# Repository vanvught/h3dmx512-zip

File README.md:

<br>[PayPal.Me Donate](https://paypal.me/AvanVught?locale.x=nl_NL)

# Orange Pi Zero / Orange Pi One
Open Source and Open Source Hardware.
<br>
## SDCard

**First time setup**: Select the uboot-*.zip for your board. Unzip the file and use an img writer; for example [Etcher](https://etcher.io).

U-Boot Orange Pi Zero: [uboot-orangpi_zero.zip](https://github.com/vanvught/h3dmx512-zip/blob/master/uboot-orangpi_zero.zip?raw=true)

U-Boot Orange Pi One: [uboot-orangpi_one.zip](https://github.com/vanvught/h3dmx512-zip/blob/master/uboot-orangpi_one.zip?raw=true)

**Firmware uImage**

Orange Pi Zero: From the zip file, copy file `orangepi_zero.uImage.gz`to the SDCard and rename to `uImage`

Orange Pi One: From the zip file, copy file `orangepi_one.uImage.gz`to the SDCard and rename to `uImage`

## Firmware uImage

* **Ethernet**
  * **Art-Net 4**
      * Pixel controller **WS28xx/SK6812/APA102/UCSx903/P9813** with DMX [Orange Pi Zero]
         * 1x 4 Universes [1x DMX] {[zip](https://github.com/vanvught/h3dmx512-zip/blob/master/opi_emac_artnet_pixel_dmx.zip?raw=true)}
         * 8x 4 Universes [2x DMX] {[zip](https://github.com/vanvught/h3dmx512-zip/blob/master/opi_emac_artnet_pixel_dmx_multi.zip?raw=true)}
      * DMX Input/Output Node / **RDM** Controller
         *  1 Port {[zip](https://github.com/vanvught/h3dmx512-zip/blob/master/opi_emac_artnet_dmx.zip?raw=true)} {*Orange Pi Zero*}
         *  2 Ports {[zip](https://github.com/vanvught/h3dmx512-zip/blob/master/opi_emac_artnet_dmx_multi.zip?raw=true)} {*Orange Pi Zero*}
         *  4 Ports {[zip](https://github.com/vanvught/h3dmx512-zip/blob/master/opi_emac_artnet_dmx_multi.zip?raw=true)} {*Orange Pi One*}
      * **Real-time Monitor** 1 Universe {[zip](https://github.com/vanvught/h3dmx512-zip/blob/master/opi_emac_artnet_monitor.zip?raw=true)} {*Orange Pi One - HDMI output*}
     * Stepper controller **L6470 RDM**
         * Sparkfun AutoDriver chaining {[zip](https://github.com/vanvught/h3dmx512-zip/blob/master/opi_emac_artnet_rdm_l6470.zip?raw=true)} {*Orange Pi Zero*}
  * **sACN E1.31** 
      * Pixel Controller **WS28xx/SK6812/APA102/UCSx903/P9813** with DMX [Orange Pi Zero]
         *  1x 4 Universes [1x DMX] {[zip](https://github.com/vanvught/h3dmx512-zip/blob/master/opi_emac_e131_pixel_dmx.zip?raw=true)}
         *  8x 4 Universes [2x DMX] {[zip](https://github.com/vanvught/h3dmx512-zip/blob/master/opi_emac_e131_pixel_dmx_multi.zip?raw=true)}
      * DMX Input / Output Bridge
         *  2 Ports {[zip](https://github.com/vanvught/h3dmx512-zip/blob/master/opi_emac_e131_dmx_multi.zip?raw=true)} {*Orange Pi Zero*}
         *  4 Ports {[zip](https://github.com/vanvught/h3dmx512-zip/blob/master/opi_emac_e131_dmx_multi.zip?raw=true)} {*Orange Pi One*}
      * **Real-time Monitor** 1 Universe {[zip](https://github.com/vanvught/h3dmx512-zip/blob/master/opi_emac_e131_monitor.zip?raw=true)} {*Orange Pi One - HDMI output*}
      * **Art-Net** converter 4/32 Universes {[zip](https://github.com/vanvught/h3dmx512-zip/blob/master/opi_emac_e131_artnet.zip?raw=true)} {*Orange Pi Zero*}
  * **Distributed Display Protocol (DDP)**
      *  Pixel Controller **WS28xx/SK6812/APA102/UCSx903/P9813** with DMX [Orange Pi Zero]
         * 8x 680 RGB or 8x 512 RGBW [2x DMX Out] {[zip](https://github.com/vanvught/h3dmx512-zip/blob/master/opi_emac_ddp_pixel_dmx_multi.zip?raw=true)}
  * **OSC** 
      * DMX Bridge {[zip](https://github.com/vanvught/h3dmx512-zip/blob/master/opi_emac_osc_dmx.zip?raw=true)}
      * Pixel Controller (WS28xx/SK6812/APA102/UCSx903/P9813) {[zip](https://github.com/vanvught/h3dmx512-zip/blob/master/opi_emac_osc_pixel.zip?raw=true)}
      * Client with support for buttons {[zip](https://github.com/vanvught/h3dmx512-zip/blob/master/opi_emac_osc_client.zip?raw=true)}
      * **Real-time Monitor** 1 Universe {[zip](https://github.com/vanvught/h3dmx512-zip/blob/master/opi_emac_osc_monitor.zip?raw=true)} {*Orange Pi One - HDMI output*}
  * **Showfile**
      *  **Player** {[zip](https://github.com/vanvught/h3dmx512-zip/blob/master/opi_emac_showfile.zip?raw=true)}
* **RDM** 
  * Controller with USB [Compatible with **Enttec USB Pro protocol**] {[zip](https://github.com/vanvught/h3dmx512-zip/blob/master/opi_dmx_usb_pro.zip?raw=true)} {*Orange Pi Zero*}
  * Responder / **DMX Pixel Controller (WS28xx/SK6812/APA102/UCSx903/P9813)** {[zip](https://github.com/vanvught/h3dmx512-zip/blob/master/opi_rdm_responder.zip?raw=true)} {*Orange Pi Zero*}
  * Stepper controller L6470
     * Sparkfun AutoDriver chaining {[zip](https://github.com/vanvught/h3dmx512-zip/blob/master/opi_rdm_responder_l6470.zip?raw=true)} {*Orange Pi Zero*}
     * Roboteurs SlushEngine Model X LT {[zip](https://github.com/vanvught/h3dmx512-zip/blob/master/opi_rdm_responder_l6470.zip?raw=true)} {*Orange Pi One*}
* **DMX**
  * **Real-time Monitor** {[zip](https://github.com/vanvught/h3dmx512-zip/blob/master/opi_dmx_monitor.zip?raw=true)} {*Orange Pi One - HDMI output*}
* **SMPTE LTC**
  * **LTC SMPTE Timecode** Reader / Writer / Generator {[zip](https://github.com/vanvught/h3dmx512-zip/blob/master/opi_emac_ltc_smpte.zip?raw=true)}  {*Orange Pi Zero*}
* **MIDI**
  *  **Real-time Monitor** {[zip](https://github.com/vanvught/h3dmx512-zip/blob/master/opi_midi_monitor.zip?raw=true)}  {*Orange Pi One - HDMI output*}

All implementations are fully according to the standards.
<br>

Detailed information can be found here : [http://www.orangepi-dmx.org](http://www.orangepi-dmx.org)

## Orange Pi Firmware Update UI
[https://github.com/vanvught/h3dmx512-Firmware-Update-UI/releases](https://github.com/vanvught/h3dmx512-Firmware-Update-UI/releases)<br>

<br>

## Remote Configuration Manager [Legacy]
[https://github.com/vanvught/Remote-Config-UI/releases](https://github.com/vanvught/Remote-Config-UI/releases)<br>

<br>

## Wireshark LUA plugin's
[https://github.com/vanvught/wireshark](https://github.com/vanvught/wireshark)

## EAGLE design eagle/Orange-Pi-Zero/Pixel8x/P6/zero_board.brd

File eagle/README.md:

# EAGLE 6.4.0 or higher
## Orange Pi Zero - prototype boards

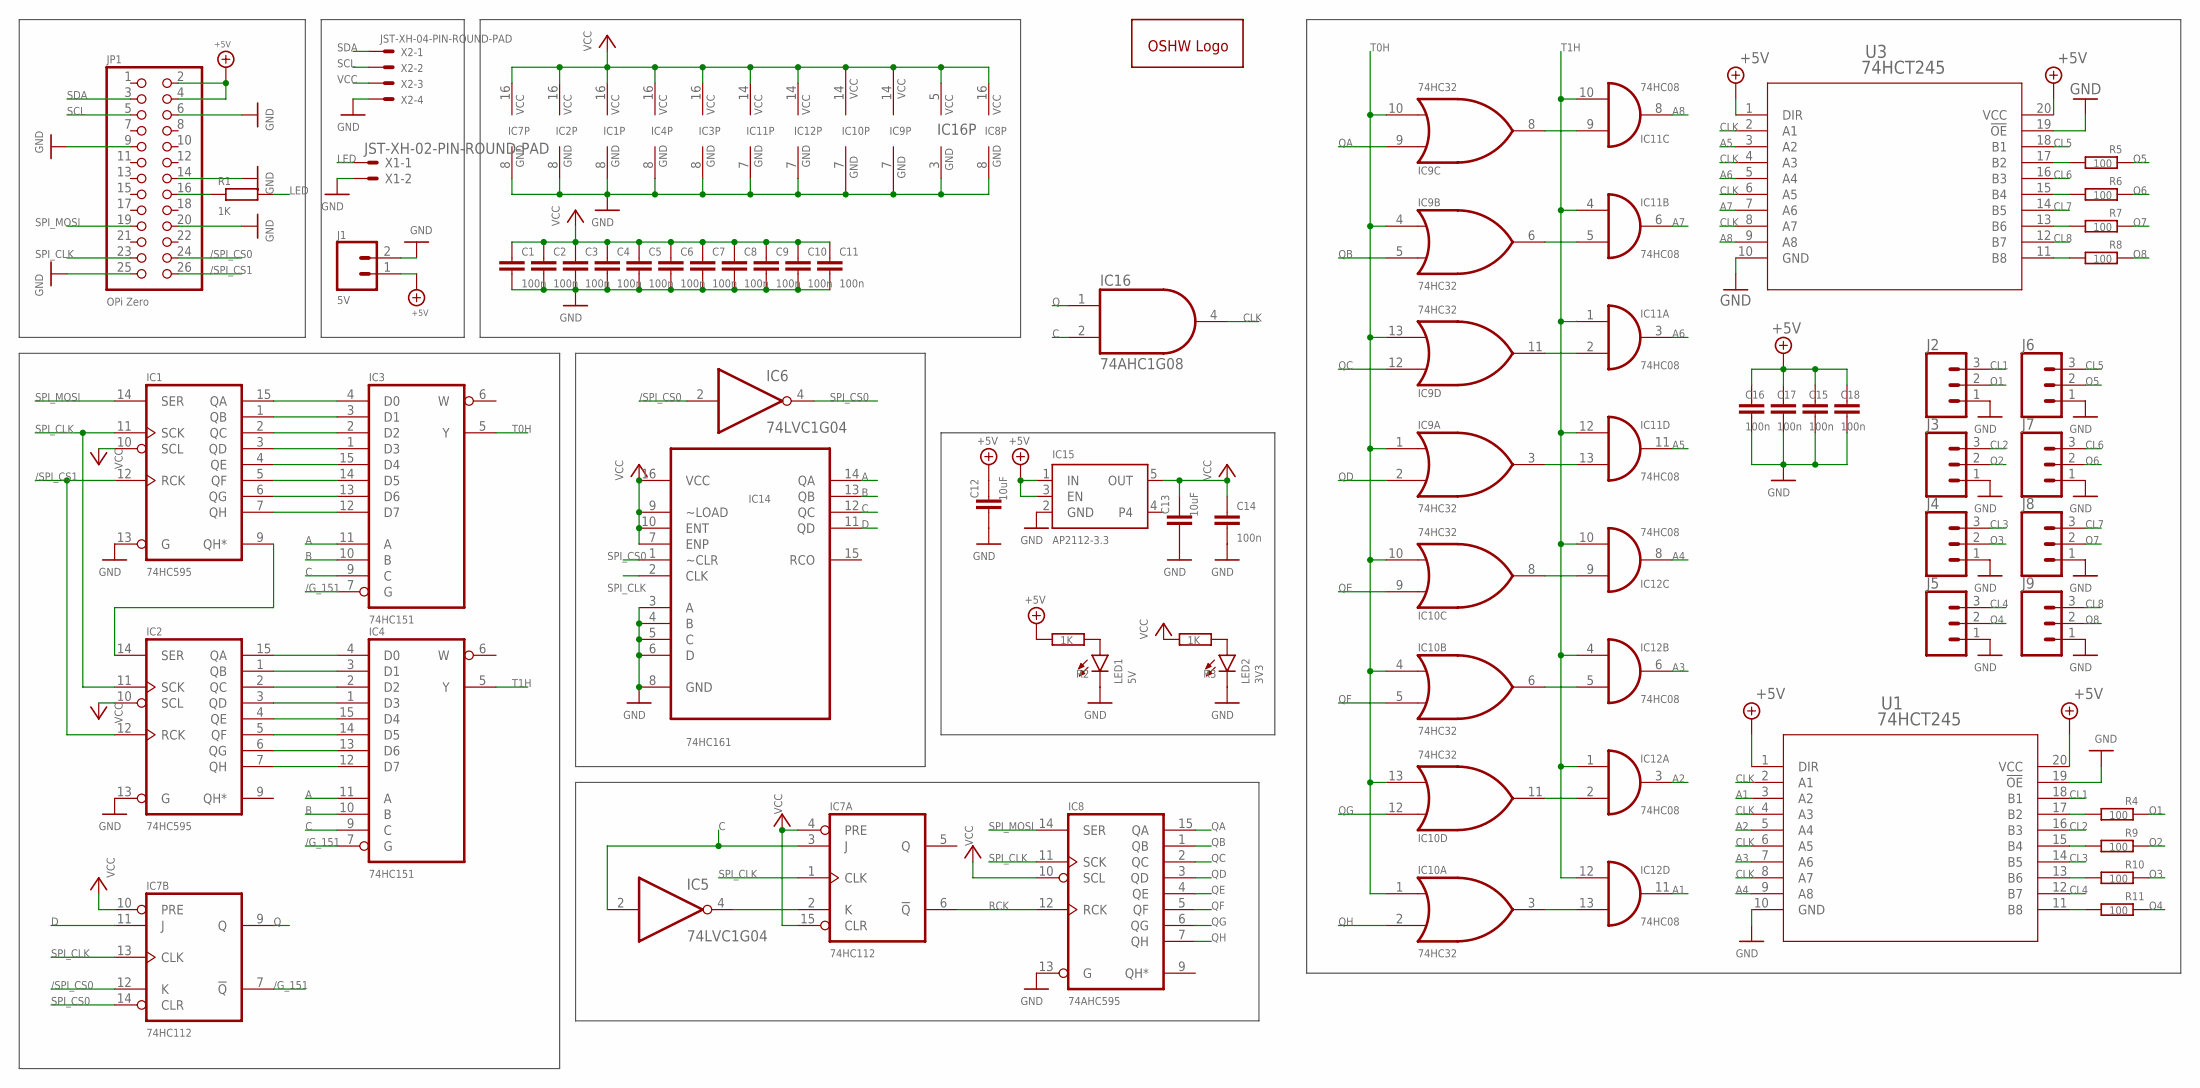
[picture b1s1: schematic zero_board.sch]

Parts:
C1, C2, C3, C4, C5, C6, C7, C8, C9, C10, C11, C14, C15, C16, C17, C18: 100n; C0603
C12, C13: 10uF; C0805
GOLD_ORB_SM1: OSHWLOGOLOGO5MM; OSHW_5MM
IC1, IC2: 74HC595; SO16
IC3, IC4: 74HC151; SO16
IC5, IC6: 74LVC1G04; SC70-5
IC7: 74HC112; SO16
IC8: 74AHC595; SO16
IC9, IC10: 74HC32; SO14
IC11, IC12: 74HC08; SO14
IC14: 74HC161; SOIC127P600X175-16N
IC15: AP2112-3.3; SOT23-5
IC16: 74AHC1G08; SC70-5
J1: 5V; SCREWTERMINAL-3.5MM-2
J2, J3, J4, J5, J6, J7, J8, J9: CONN_03SCREW-NS; SCREWTERMINAL-3.5MM-3-NS
JP1: OPi Zero; 2X13
LED1: 5V; CHIP-LED0603
LED2: 3V3; CHIP-LED0603
R1, R2, R3: 1K; R0603
R4, R5, R6, R7, R8, R9, R10, R11: 100; R0603
U1, U3: 74HCT245; PW20
X1: JST-XH-02-PIN-ROUND-PAD; JST-XH-02-PACKAGE-ROUND-PAD
X2: JST-XH-04-PIN-ROUND-PAD; JST-XH-04-PACKAGE-ROUND-PAD

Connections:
+5V: C12.1, C15.1, C16.1, C17.1, C18.1, IC15.1 (IN), IC15.3 (EN), J1.1, JP1.2, JP1.4, R2.1, U1.1 (DIR), U1.20 (VCC), U3.1 (DIR), U3.20 (VCC)
/G_151: IC3.7 (G), IC4.7 (G), IC7.7 (!Q)
/SPI_CS0: IC6.2 (I), IC7.12 (K), JP1.24
/SPI_CS1: IC1.12 (RCK), IC2.12 (RCK), JP1.26
A: IC3.11 (A), IC4.11 (A), IC14.14 (QA)
A1: IC12.11 (O), U1.3 (A2)
A2: IC12.3 (O), U1.5 (A4)
A3: IC12.6 (O), U1.7 (A6)
A4: IC12.8 (O), U1.9 (A8)
A5: IC11.11 (O), U3.3 (A2)
A6: IC11.3 (O), U3.5 (A4)
A7: IC11.6 (O), U3.7 (A6)
A8: IC11.8 (O), U3.9 (A8)
B: IC3.10 (B), IC4.10 (B), IC14.13 (QB)
C: IC3.9 (C), IC4.9 (C), IC5.2 (I), IC7.3 (J), IC14.12 (QC), IC16.2 (I1)
CL1: J2.3, U1.18 (B1)
CL2: J3.3, U1.16 (B3)
CL3: J4.3, U1.14 (B5)
CL4: J5.3, U1.12 (B7)
CL5: J6.3, U3.18 (B1)
CL6: J7.3, U3.16 (B3)
CL7: J8.3, U3.14 (B5)
CL8: J9.3, U3.12 (B7)
CLK: IC16.4 (O), U1.2 (A1), U1.4 (A3), U1.6 (A5), U1.8 (A7), U3.2 (A1), U3.4 (A3), U3.6 (A5), U3.8 (A7)
D: IC7.11 (J), IC14.11 (QD)
GND: C1.2, C2.2, C3.2, C4.2, C5.2, C6.2, C7.2, C8.2, C9.2, C10.2, C11.2, C12.2, C13.2, C14.2, C15.2, C16.2, C17.2, C18.2, IC1.8 (GND), IC1.13 (G), IC2.8 (GND), IC2.13 (G), IC3.8 (GND), IC4.8 (GND), IC5.3 (GND), IC6.3 (GND), IC7.8 (GND), IC8.8 (GND), IC8.13 (G), IC9.7 (GND), IC10.7 (GND), IC11.7 (GND), IC12.7 (GND), IC14.3 (A), IC14.4 (B), IC14.5 (C), IC14.6 (D), IC14.8 (GND), IC15.2 (GND), IC16.3 (GND), J1.2, J2.1, J3.1, J4.1, J5.1, J6.1, J7.1, J8.1, J9.1, JP1.6, JP1.9, JP1.14, JP1.20, JP1.25, LED1.C, LED2.C, U1.10 (GND), U1.19 (!OE), U3.10 (GND), U3.19 (!OE), X1.2, X2.4
LED: R1.2, X1.1
unnamed: IC10.11 (O), IC12.2 (I1)
unnamed: IC10.6 (O), IC12.5 (I1)
unnamed: IC10.8 (O), IC12.9 (I0)
unnamed: IC10.3 (O), IC12.13 (I1)
unnamed: IC9.8 (O), IC11.9 (I0)
unnamed: IC9.6 (O), IC11.5 (I1)
unnamed: IC9.11 (O), IC11.2 (I1)
unnamed: JP1.16, R1.1
unnamed: R11.1, U1.11 (B8)
unnamed: R8.1, U3.11 (B8)
unnamed: IC1.15 (QA), IC3.4 (D0)
unnamed: IC1.1 (QB), IC3.3 (D1)
unnamed: IC1.2 (QC), IC3.2 (D2)
unnamed: IC1.3 (QD), IC3.1 (D3)
unnamed: IC5.4 (O), IC7.2 (K)
unnamed: IC9.3 (O), IC11.13 (I1)
unnamed: R7.1, U3.13 (B6)
unnamed: IC2.15 (QA), IC4.4 (D0)
unnamed: R10.1, U1.13 (B6)
unnamed: IC1.4 (QE), IC3.15 (D4)
unnamed: IC1.5 (QF), IC3.14 (D5)
unnamed: IC1.6 (QG), IC3.13 (D6)
unnamed: IC1.7 (QH), IC3.12 (D7)
unnamed: IC2.1 (QB), IC4.3 (D1)
unnamed: R6.1, U3.15 (B4)
unnamed: IC2.2 (QC), IC4.2 (D2)
unnamed: IC2.3 (QD), IC4.1 (D3)
unnamed: IC2.4 (QE), IC4.15 (D4)
unnamed: IC2.5 (QF), IC4.14 (D5)
unnamed: IC2.6 (QG), IC4.13 (D6)
unnamed: IC2.7 (QH), IC4.12 (D7)
unnamed: R5.1, U3.17 (B2)
unnamed: LED1.A, R2.2
unnamed: LED2.A, R3.2
unnamed: R9.1, U1.15 (B4)
unnamed: R4.1, U1.17 (B2)
unnamed: IC1.9 (QH*), IC2.14 (SER)
O1: J2.2, R4.2
O2: J3.2, R9.2
O3: J4.2, R10.2
O4: J5.2, R11.2
O5: J6.2, R5.2
O6: J7.2, R6.2
O7: J8.2, R7.2
O8: J9.2, R8.2
Q: IC7.9 (Q), IC16.1 (I0)
QA: IC8.15 (QA), IC9.9 (I0)
QB: IC8.1 (QB), IC9.5 (I1)
QC: IC8.2 (QC), IC9.12 (I0)
QD: IC8.3 (QD), IC9.2 (I1)
QE: IC8.4 (QE), IC10.9 (I0)
QF: IC8.5 (QF), IC10.5 (I1)
QG: IC8.6 (QG), IC10.12 (I0)
QH: IC8.7 (QH), IC10.2 (I1)
RCK: IC7.6 (!Q), IC8.12 (RCK)
SCL: JP1.5, X2.2
SDA: JP1.3, X2.1
SPI_CLK: IC1.11 (SCK), IC2.11 (SCK), IC7.1 (CLK), IC7.13 (CLK), IC8.11 (SCK), IC14.2 (CLK), JP1.23
SPI_CS0: IC6.4 (O), IC7.14 (CLR), IC14.1 (~CLR)
SPI_MOSI: IC1.14 (SER), IC8.14 (SER), JP1.19
T0H: IC3.5 (Y), IC9.1 (I0), IC9.4 (I0), IC9.10 (I1), IC9.13 (I1), IC10.1 (I0), IC10.4 (I0), IC10.10 (I1), IC10.13 (I1)
T1H: IC4.5 (Y), IC11.1 (I0), IC11.4 (I0), IC11.10 (I1), IC11.12 (I0), IC12.1 (I0), IC12.4 (I0), IC12.10 (I1), IC12.12 (I0)
VCC: C1.1, C2.1, C3.1, C4.1, C5.1, C6.1, C7.1, C8.1, C9.1, C10.1, C11.1, C13.1, C14.1, IC1.10 (SCL), IC1.16 (VCC), IC2.10 (SCL), IC2.16 (VCC), IC3.16 (VCC), IC4.16 (VCC), IC5.5 (VCC), IC6.5 (VCC), IC7.4 (PRE), IC7.10 (PRE), IC7.15 (CLR), IC7.16 (VCC), IC8.10 (SCL), IC8.16 (VCC), IC9.14 (VCC), IC10.14 (VCC), IC11.14 (VCC), IC12.14 (VCC), IC14.7 (ENP), IC14.9 (~LOAD), IC14.10 (ENT), IC14.16 (VCC), IC15.5 (OUT), IC16.5 (VCC), R3.1, X2.3

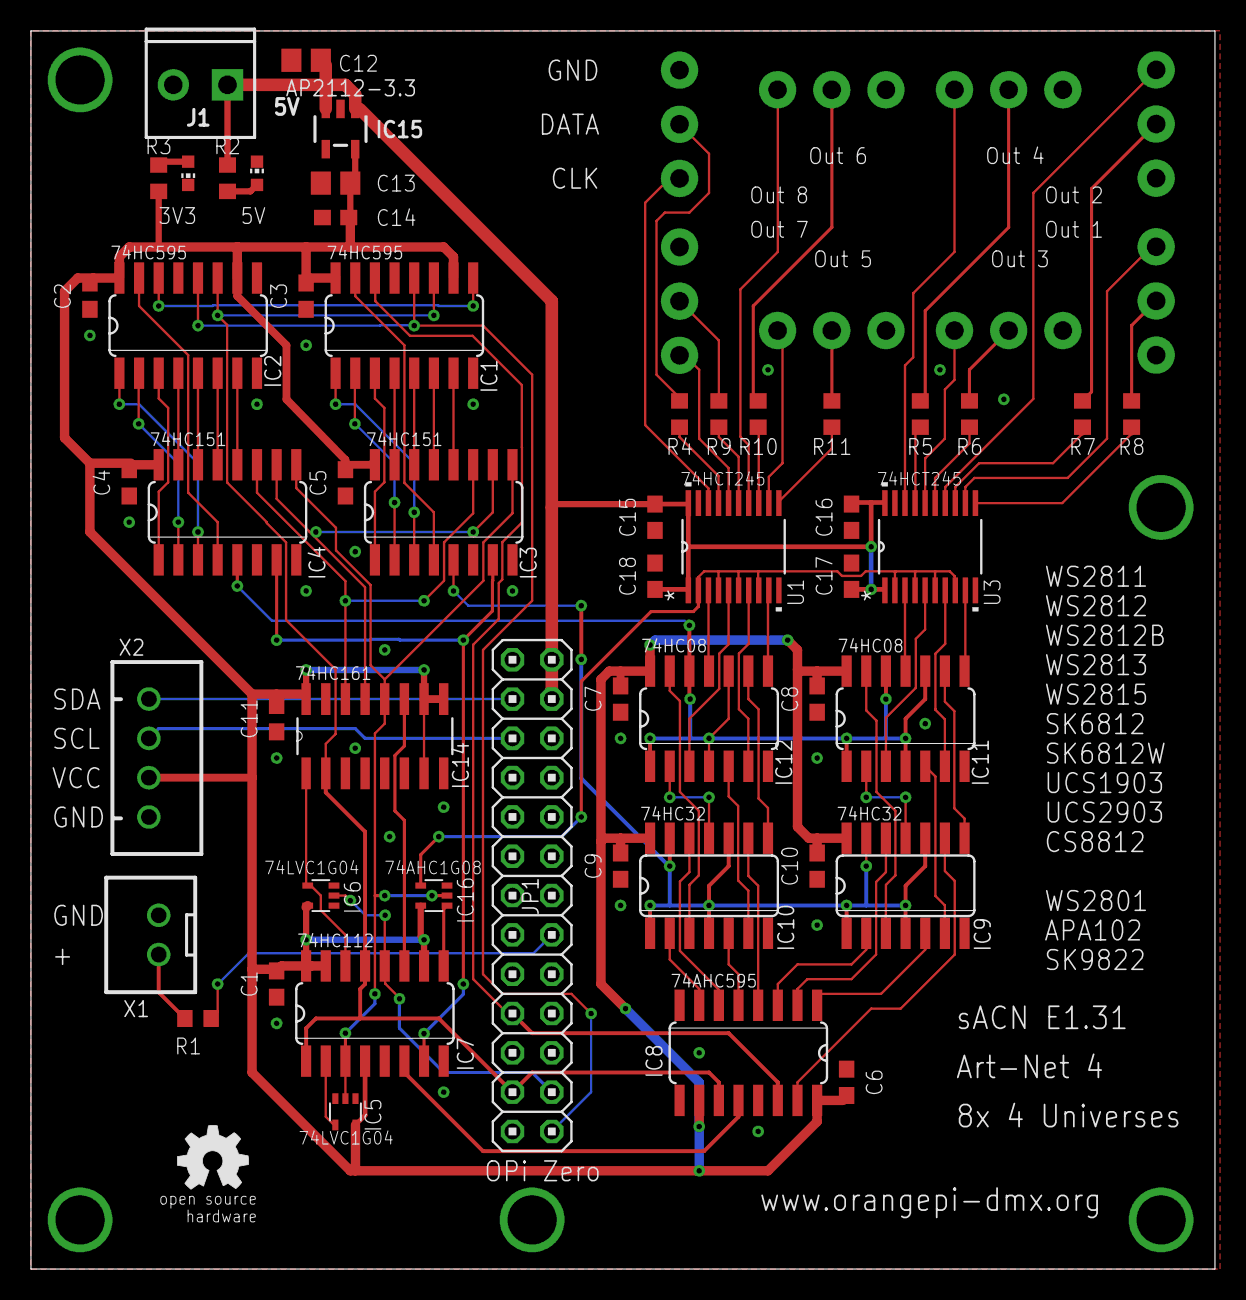
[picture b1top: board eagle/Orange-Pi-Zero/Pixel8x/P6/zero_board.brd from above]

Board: 2 copper layers, 76.5 x 80.0 mm, 61 parts (0 on the bottom side), 90 nets.

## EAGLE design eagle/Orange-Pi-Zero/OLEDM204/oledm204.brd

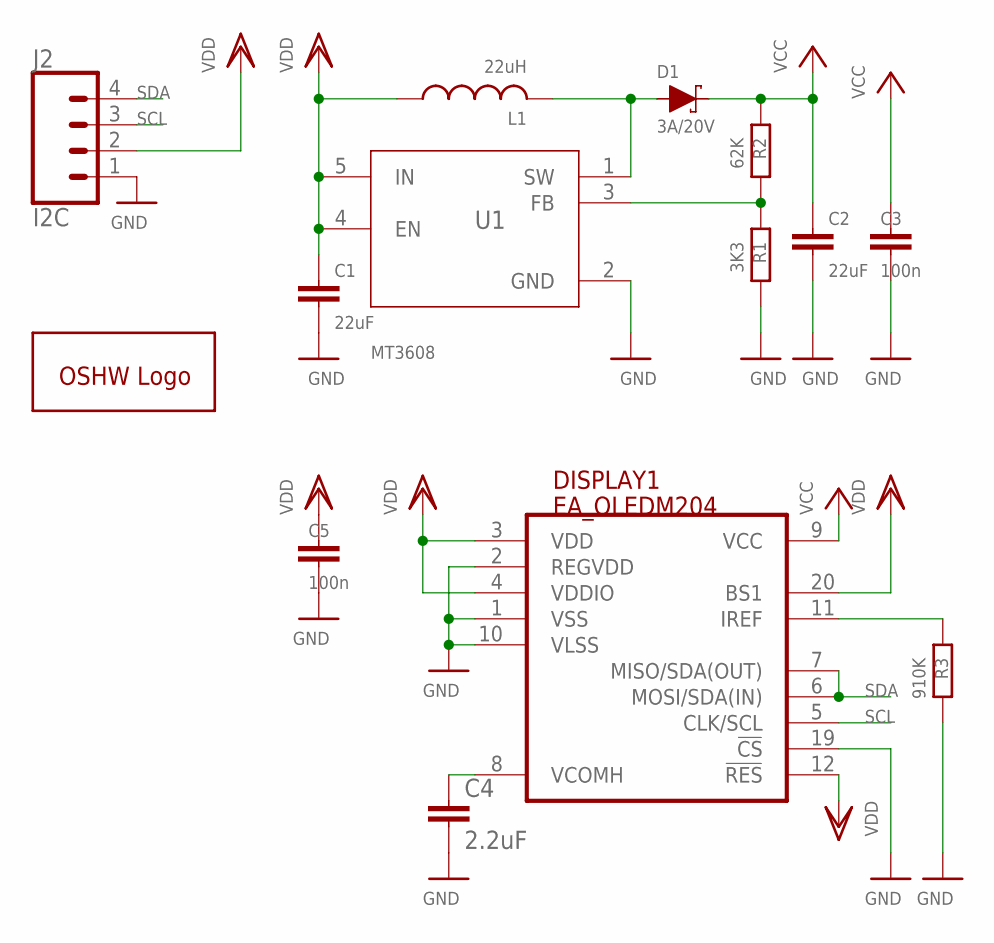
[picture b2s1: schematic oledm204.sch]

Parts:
C1, C2: 22uF; C0603
C3, C5: 100n; C0603
C4: 2.2uF; C0603
D1: 3A/20V; SMA-DIODE
DISPLAY1: EA_OLEDM204
GOLD_ORB_SM1: OSHWLOGOLOGO5MM; OSHW_5MM
J2: I2C; 1X04
L1: 22uH; PIS2816
R1: 3K3; R0402
R2: 62K; R0402
R3: 910K; R0402
U1: MT3608; SOT95P280X145-6N

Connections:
GND: C1.2, C2.2, C3.2, C4.2, C5.2, DISPLAY1.1 (VSS), DISPLAY1.2 (REGVDD), DISPLAY1.10 (VLSS), DISPLAY1.19 (!CS!), J2.1, R1.2, R3.2, U1.2 (GND)
unnamed: DISPLAY1.11 (IREF), R3.1
unnamed: R1.1, R2.2, U1.3 (FB)
unnamed: D1.A, L1.2, U1.1 (SW)
unnamed: C4.1, DISPLAY1.8 (VCOMH)
SCL: DISPLAY1.5 (CLK/SCL), J2.3
SDA: DISPLAY1.6 (MOSI/SDA(IN)), DISPLAY1.7 (MISO/SDA(OUT)), J2.4
VCC: C2.1, C3.1, D1.C, DISPLAY1.9 (VCC), R2.1
VDD: C1.1, C5.1, DISPLAY1.3 (VDD), DISPLAY1.4 (VDDIO), DISPLAY1.12 (!RES!), DISPLAY1.20 (BS1), J2.2, L1.1, U1.4 (EN), U1.5 (IN)

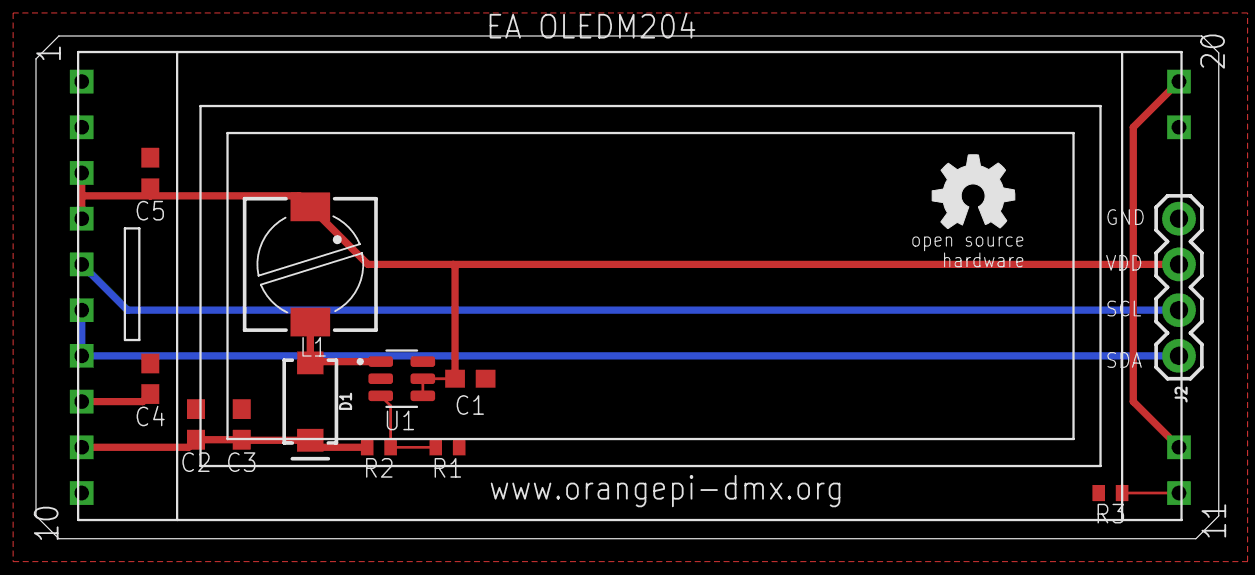
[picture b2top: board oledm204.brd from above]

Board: 2 copper layers, 65.7 x 27.9 mm, 14 parts (0 on the bottom side), 9 nets.

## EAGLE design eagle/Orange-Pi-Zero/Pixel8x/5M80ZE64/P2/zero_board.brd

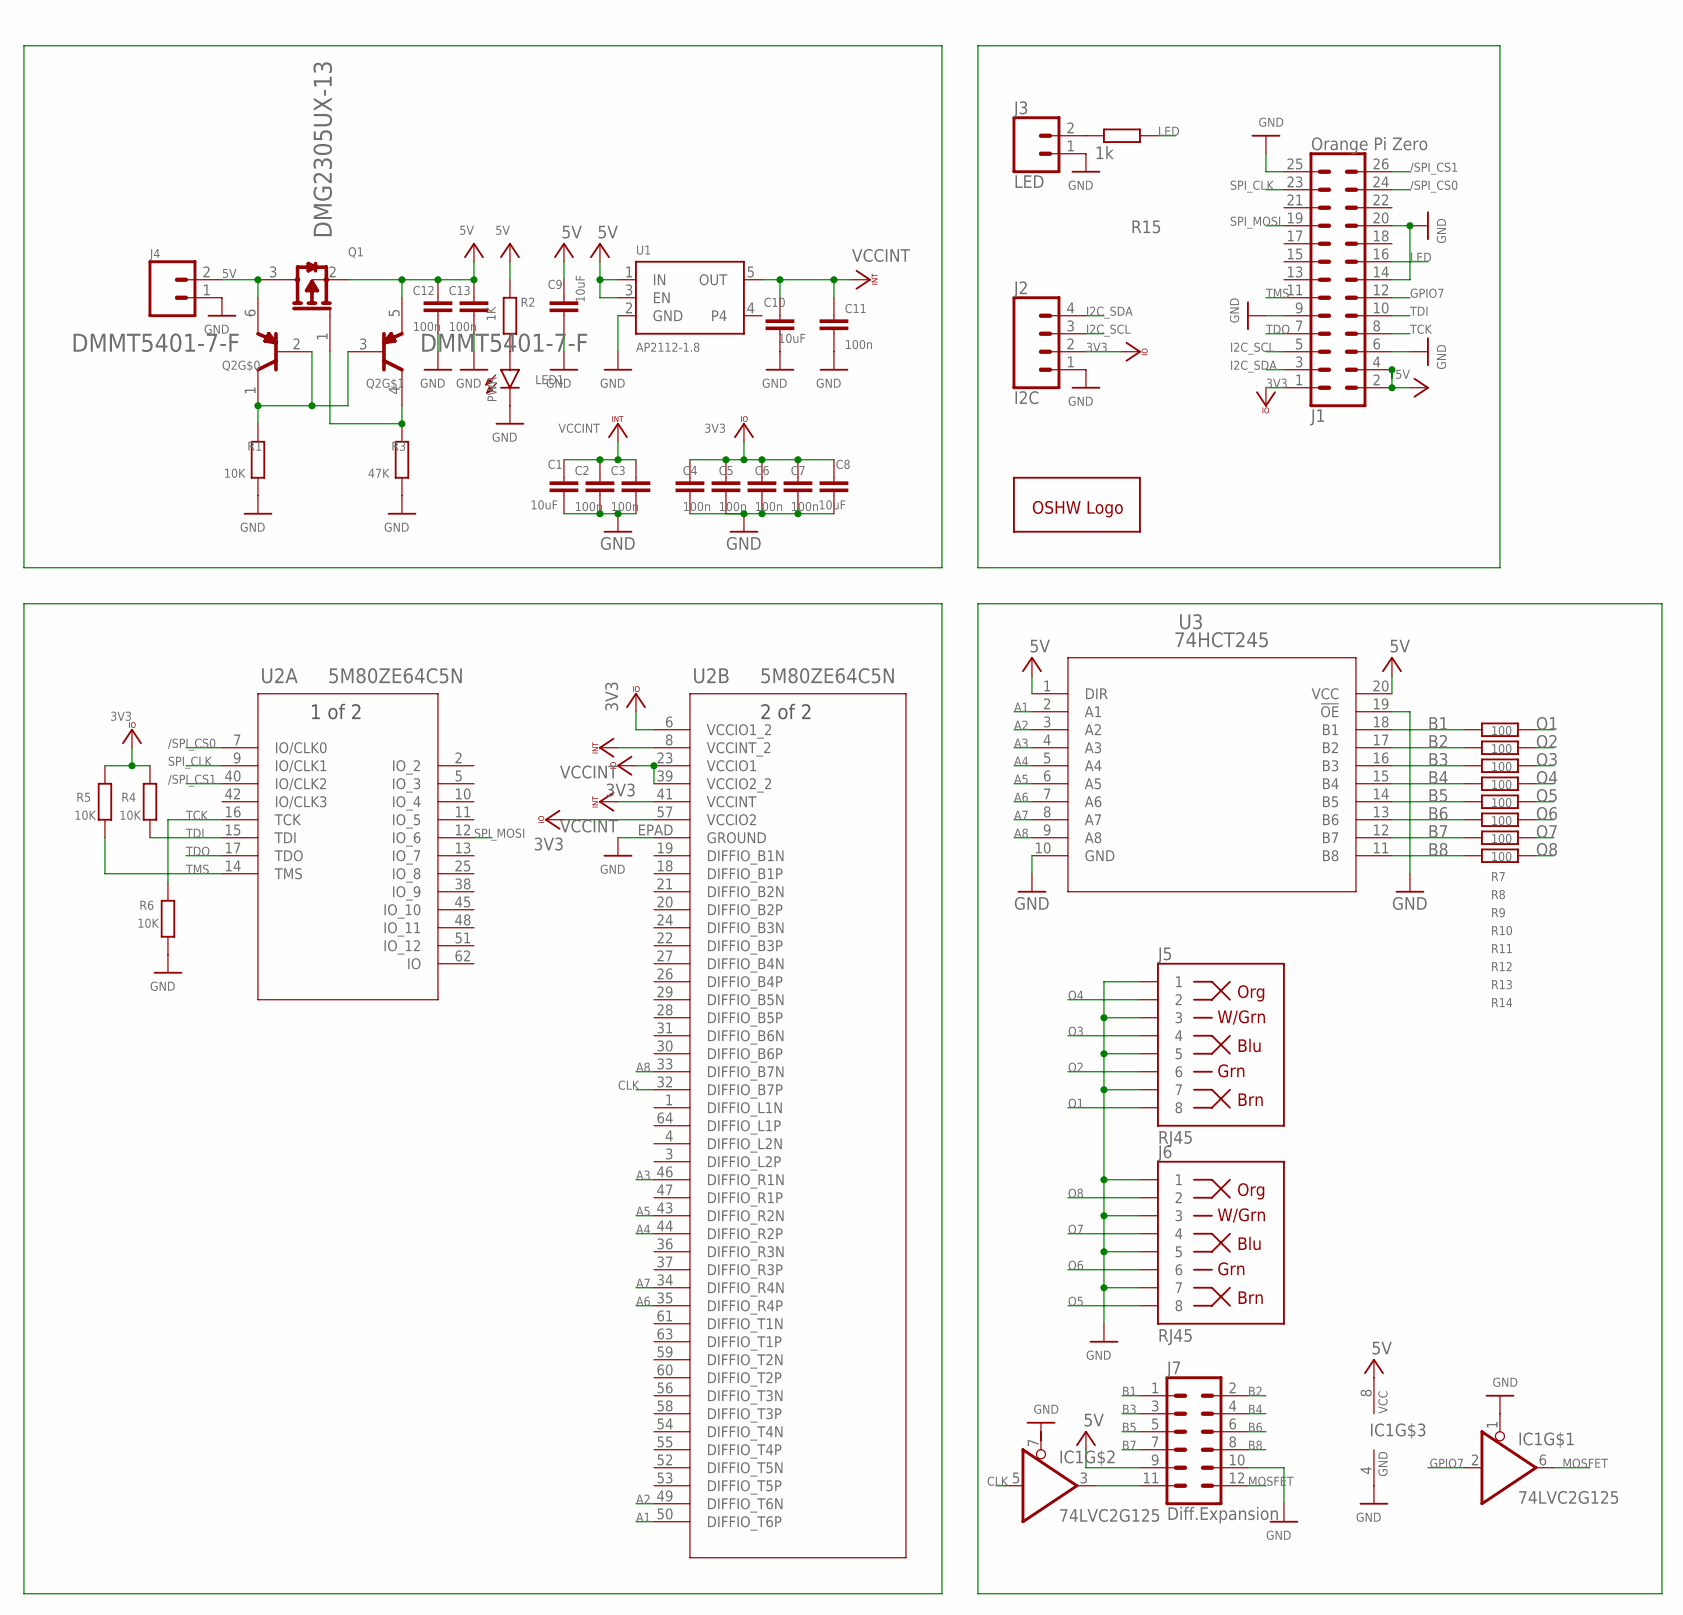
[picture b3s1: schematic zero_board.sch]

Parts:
C1, C8, C9, C10: 10uF; C0805
C2, C3, C4, C5, C6, C7, C11, C12, C13: 100n; C0603
GOLD_ORB_SM1: OSHWLOGOLOGO5MM; OSHW_5MM
IC1: 74LVC2G125; SSOP08
J1: Orange Pi Zero; 2X13
J2: I2C; 1X04
J3: LED; 1X02
J4: 5V; SCREWTERMINAL-3.5MM-2
J5, J6: RJ45; RJ45-8
J7: Diff.Expansion; 2X6
LED1: PWR; CHIP-LED0603
Q1: DIODES_INC._DMG2305UX-13DIODES_INC._DMG2305UX-13_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; DIODES_INC._DMG2305UX-13_0
Q2: DMMT5401-7-F_0_0; DIODES_DMMT5401-7-F_0
R1, R4, R5, R6: 10K; R0402
R2: 1K; R0402
R3: 47K; R0402
R7, R8, R9, R10, R11, R12, R13, R14: 100; R0402
R15: 1k; R0402
U1: AP2112-1.8; SOT23-5
U2: 5M80ZE64C5N; EQFP64P_A1P2-D4P5_INT-L
U3: 74HCT245; PW20

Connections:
/SPI_CS0: J1.24, U2.7 (IO/CLK0)
/SPI_CS1: J1.26, U2.40 (IO/CLK2)
A1: U2.50 (DIFFIO_T6P), U3.2 (A1)
A2: U2.49 (DIFFIO_T6N), U3.3 (A2)
A3: U2.46 (DIFFIO_R1N), U3.4 (A3)
A4: U2.44 (DIFFIO_R2P), U3.5 (A4)
A5: U2.43 (DIFFIO_R2N), U3.6 (A5)
A6: U2.35 (DIFFIO_R4P), U3.7 (A6)
A7: U2.34 (DIFFIO_R4N), U3.8 (A7)
A8: U2.33 (DIFFIO_B7N), U3.9 (A8)
B1: J7.1, R7.1, U3.18 (B1)
B2: J7.2, R8.1, U3.17 (B2)
B3: J7.3, R9.1, U3.16 (B3)
B4: J7.4, R10.1, U3.15 (B4)
B5: J7.5, R11.1, U3.14 (B5)
B6: J7.6, R12.1, U3.13 (B6)
B7: J7.7, R13.1, U3.12 (B7)
B8: J7.8, R14.1, U3.11 (B8)
CLK: IC1.5 (I), U2.32 (DIFFIO_B7P)
GND: C1.2, C2.2, C3.2, C4.2, C5.2, C6.2, C7.2, C8.2, C9.2, C10.2, C11.2, C12.2, C13.2, IC1.1 (OE), IC1.4 (GND), J1.6, J1.9, J1.14, J1.20, J1.25, J2.1, J3.1, J4.1, J5.1, J5.3, J5.5, J5.7, J6.1, J6.3, J6.5, J6.7, J7.10, LED1.C, R1.1, R3.1, R6.1, U1.2 (GND), U2.EPAD (GROUND), U3.10 (GND), U3.19 (!OE)
GPIO7: IC1.2 (I), J1.12
I2C_SCL: J1.5, J2.3
I2C_SDA: J1.3, J2.4
LED: J1.16, R15.2
MOSFET: IC1.6 (O), J7.12
unnamed: Q2.1 (C1), Q2.2 (B1), Q2.3 (B2), R1.2
unnamed: J4.2, Q1.3 (D), Q2.6 (E1)
unnamed: Q1.1 (G), Q2.4 (C2), R3.2
unnamed: J3.2, R15.1
unnamed: IC1.3 (O), J7.11
unnamed: LED1.A, R2.2
O1: J5.8, R7.2
O2: J5.6, R8.2
O3: J5.4, R9.2
O4: J5.2, R10.2
O5: J6.8, R11.2
O6: J6.6, R12.2
O7: J6.4, R13.2
O8: J6.2, R14.2
SPI_CLK: J1.23, U2.9 (IO/CLK1)
SPI_MOSI: J1.19, U2.12 (IO_6)
TCK: J1.8, R6.2, U2.16 (TCK)
TDI: J1.10, R4.1, U2.15 (TDI)
TDO: J1.7, U2.17 (TDO)
TMS: J1.11, R5.1, U2.14 (TMS)
VCC: C9.1, C12.1, C13.1, IC1.8 (VCC), J1.2, J1.4, J7.9, Q1.2 (S), Q2.5 (E2), R2.1, U1.1 (IN), U1.3 (EN), U3.1 (DIR), U3.20 (VCC)
VCCINT: C1.1, C2.1, C3.1, C10.1, C11.1, U1.5 (OUT), U2.8 (VCCINT_2), U2.41 (VCCINT)
VCCIO: C4.1, C5.1, C6.1, C7.1, C8.1, J1.1, J2.2, R4.2, R5.2, U2.6 (VCCIO1_2), U2.23 (VCCIO1), U2.39 (VCCIO2_2), U2.57 (VCCIO2)

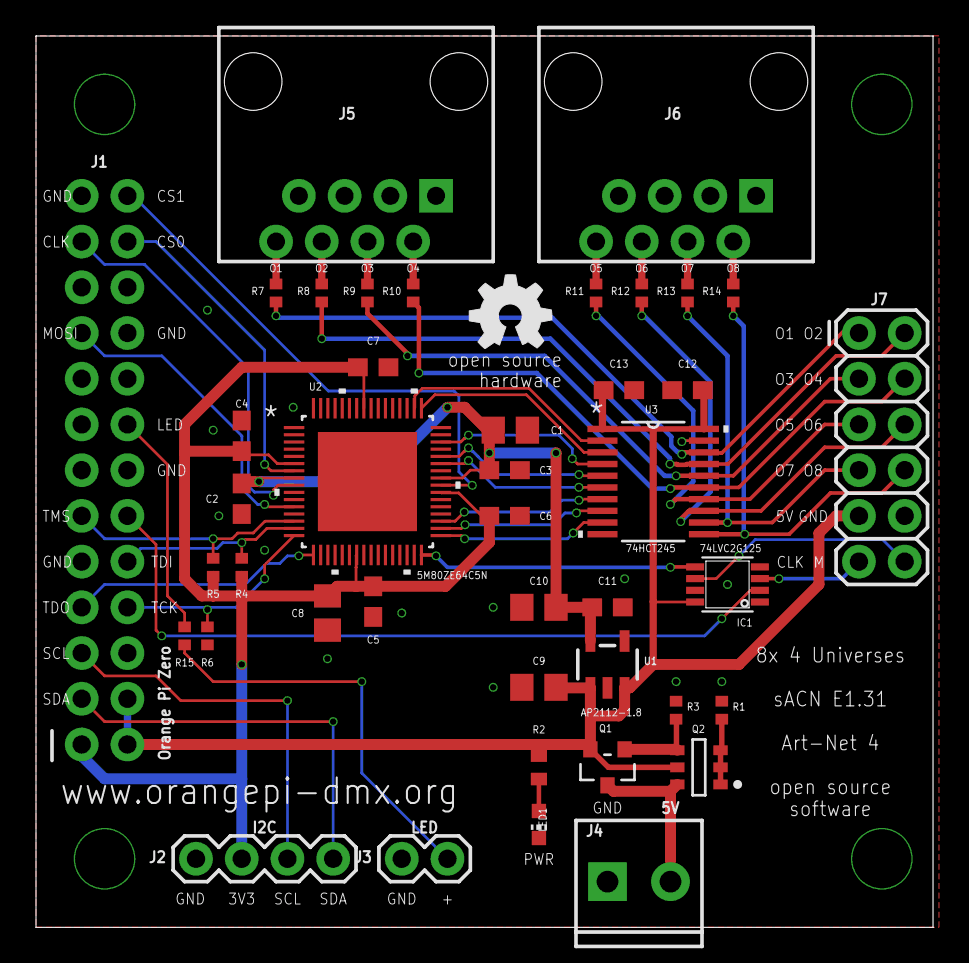
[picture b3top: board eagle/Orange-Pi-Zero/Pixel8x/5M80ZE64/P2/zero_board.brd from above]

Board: 2 copper layers, 49.8 x 49.5 mm, 43 parts (1 on the bottom side), 48 nets.

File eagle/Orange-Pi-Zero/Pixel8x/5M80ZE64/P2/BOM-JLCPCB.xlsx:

Qty | Designator | Footprint | Comment | LCSC Part #
1 | LED1 | CHIP-LED0603 | LED GREEN 0603 | C72043
9 | C2, C3, C4, C5, C6, C7, C11, C12, C13 | C0603 | 100n | C14663
4 | C1, C8, C9, C10 | C0805 | 10uF | C90545
2 | R2, R15 | R0402 | 1K | C11702
8 | R7, R8, R9, R10, R11, R12, R13, R14 | R0402 | 100 | C25076
4 | R1, R4, R5, R6 | R0402 | 10K | C25744
1 | R3 | R0402 | 47K | C25792
1 | U1 | SOT25 | AP2112K-1.8TRG1 | C176944
1 | U2 | TQFP-64 | 5M80ZE64C5N | C470829
1 | U3 | SSOP-20 | 74AHCT245 | C10910
1 | Q1 | SOT-23-3 | DMG2305UX-13 | C144153
1 | Q2 | SOT-23-6L | DMMT5401-7 | C154733
1 | IC1 | SSOP08 | 74LVC2G125DCT | C206035
35

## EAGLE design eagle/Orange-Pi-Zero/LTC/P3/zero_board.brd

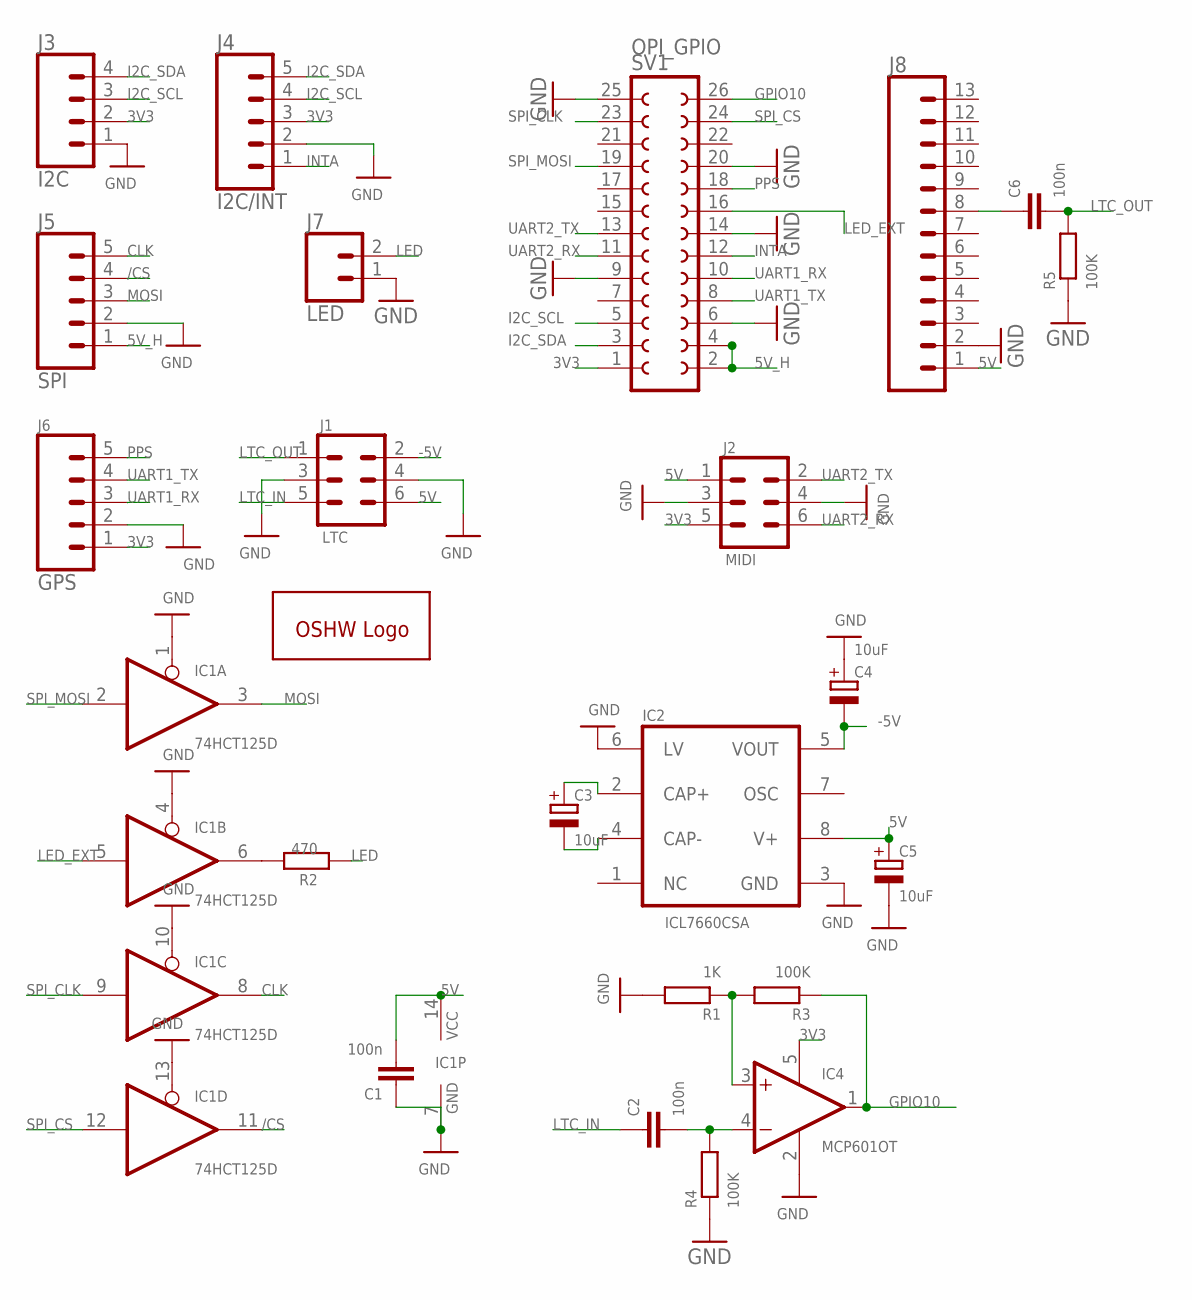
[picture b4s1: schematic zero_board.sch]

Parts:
C1, C2, C6: 100n; C0603
C3, C4, C5: 10uF; 153CLV-0405
GOLD_ORB_SM1: OSHWLOGOLOGO5MM; OSHW_5MM
IC1: 74HCT125D; SO14
IC2: ICL7660CSA; SO08
IC4: MCP601OT; SOT23-5
J1: LTC; 2X3
J2: MIDI; 2X3-SHROUDED
J3: I2C; 1X04
J4: I2C/INT; 1X05
J5: SPI; 1X05
J6: GPS; 1X05
J7: LED; 1X02
J8: CONN_13; 1X13
R1: 1K; R0603
R2: 470; R0603
R3, R4, R5: 100K; R0603
SV1: OPI_GPIO; FE13-2

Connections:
3V3: IC4.5 (V+), J2.5, J3.2, J4.3, J6.1, SV1.1
5V: C1.2, C5.+, IC1.14 (VCC), IC2.8 (V+), J1.6, J2.1, J8.1
5V_H: J5.1, SV1.2, SV1.4
-5V: C4.-, IC2.5 (VOUT), J1.2
/CS: IC1.11 (O), J5.4
CLK: IC1.8 (O), J5.5
GND: C1.1, C4.+, C5.-, IC1.1 (OE), IC1.4 (OE), IC1.7 (GND), IC1.10 (OE), IC1.13 (OE), IC2.3 (GND), IC2.6 (LV), IC4.2 (V-), J1.3, J1.4, J2.3, J2.4, J3.1, J4.2, J5.2, J6.2, J7.1, J8.2, R1.2, R4.1, R5.1, SV1.6, SV1.9, SV1.14, SV1.20, SV1.25
GPIO10: IC4.1 (OUT), R3.1, SV1.26
I2C_SCL: J3.3, J4.4, SV1.5
I2C_SDA: J3.4, J4.5, SV1.3
INTA: J4.1, SV1.12
LED: J7.2, R2.1
LED_EXT: IC1.5 (I), SV1.16
LINE_OUT_L: C6.1, J8.8
LTC_IN: C2.1, J1.5
LTC_OUT: C6.2, J1.1, R5.2
MOSI: IC1.3 (O), J5.3
unnamed: IC1.6 (O), R2.2
unnamed: C2.2, IC4.4 (-IN), R4.2
unnamed: IC4.3 (+IN), R1.1, R3.2
unnamed: C3.+, IC2.2 (CAP+)
unnamed: C3.-, IC2.4 (CAP-)
PPS: J6.5, SV1.18
SPI_CLK: IC1.9 (I), SV1.23
SPI_CS: IC1.12 (I), SV1.24
SPI_MOSI: IC1.2 (I), SV1.19
UART1_RX: J6.3, SV1.10
UART1_TX: J6.4, SV1.8
UART2_RX: J2.6, SV1.11
UART2_TX: J2.2, SV1.13

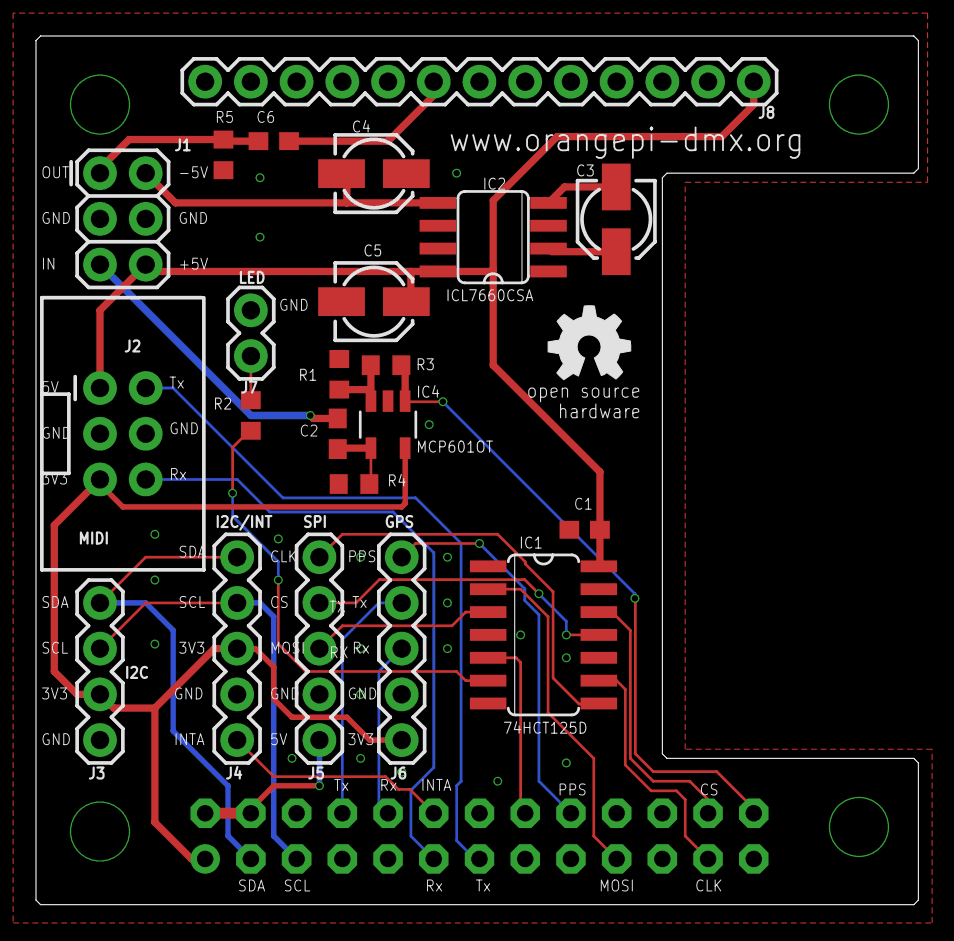
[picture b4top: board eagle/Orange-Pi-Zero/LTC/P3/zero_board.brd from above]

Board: 2 copper layers, 49.0 x 48.3 mm, 24 parts (1 on the bottom side), 30 nets.

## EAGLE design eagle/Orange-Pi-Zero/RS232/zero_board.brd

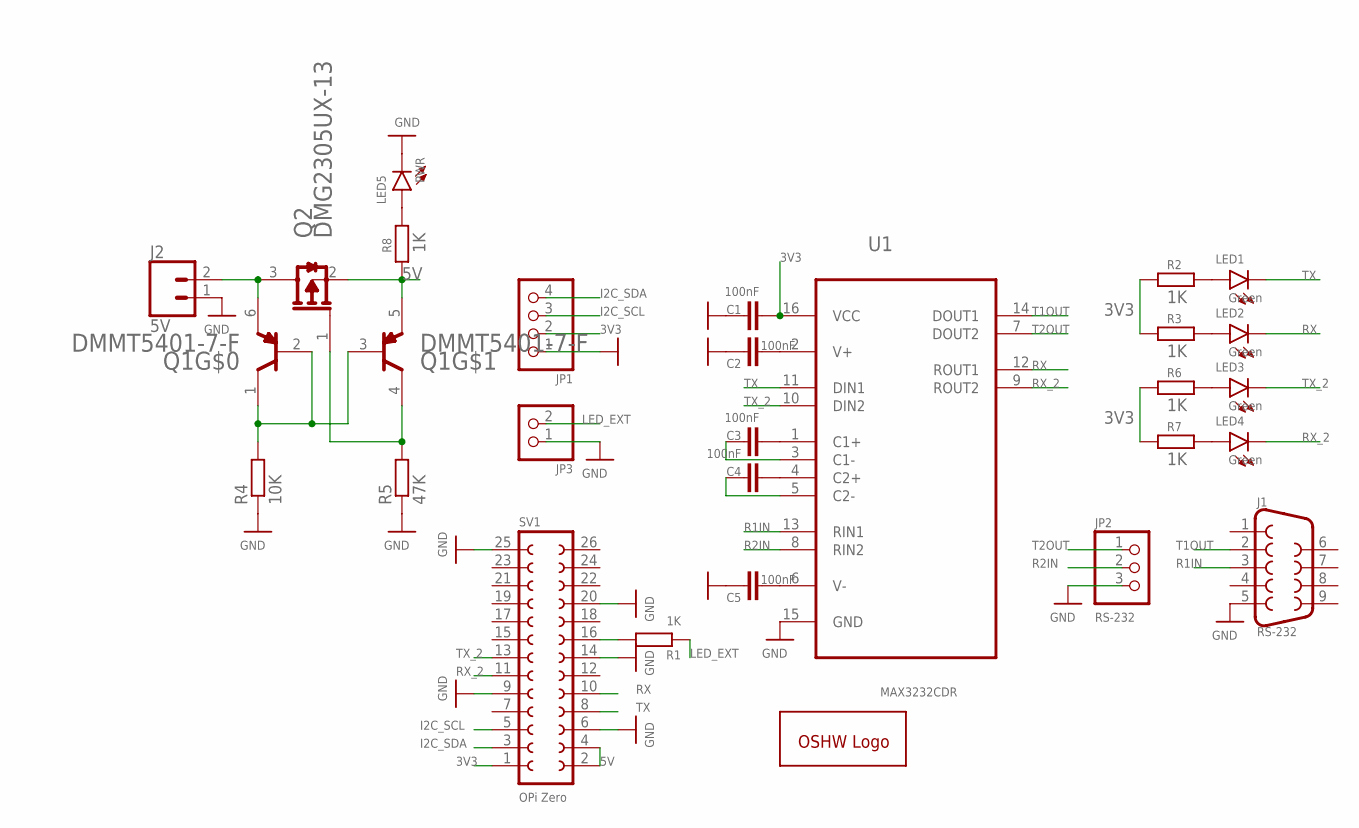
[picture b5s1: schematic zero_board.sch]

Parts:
C1, C2, C3, C4, C5: 100nF; C0603
GOLD_ORB_SM1: OSHWLOGOLOGO5MM; OSHW_5MM
J1: RS-232; DB9
J2: 5V; SCREWTERMINAL-3.5MM-2
JP1: OLED; 1X04
JP2: RS-232; 1X03
JP3: LED; 1X02
LED1, LED2, LED3, LED4: Green; CHIP-LED0603
LED5: PWR; CHIP-LED0603
Q1: DIODES_DMMT5401-7-FDIODES_DMMT5401-7-F_0_0; DIODES_DMMT5401-7-F_0
Q2: DIODES_INC._DMG2305UX-13DIODES_INC._DMG2305UX-13_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; DIODES_INC._DMG2305UX-13_0
R1, R2, R3, R6, R7, R8: 1K; R0603
R4: 10K; R0402
R5: 47K; R0402
SV1: OPi Zero; FE13-2
U1: MAX3232CDR; SOIC127P600X175-16N

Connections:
3V3: C1.2, JP1.2, R2.1, R3.1, R6.1, R7.1, SV1.1, U1.16 (VCC)
5V: Q1.5 (E2), Q2.2 (S), R8.1, SV1.2, SV1.4
GND: C1.1, C2.1, C5.1, J1.5, J2.1, JP1.1, JP2.3, JP3.1, LED5.C, R4.1, R5.1, SV1.6, SV1.9, SV1.14, SV1.20, SV1.25, U1.15 (GND)
I2C_SCL: JP1.3, SV1.5
I2C_SDA: JP1.4, SV1.3
LED_EXT: JP3.2, R1.1
unnamed: C4.1, U1.5 (C2-)
unnamed: C2.2, U1.2 (V+)
unnamed: C3.1, U1.3 (C1-)
unnamed: R1.2, SV1.16
unnamed: C3.2, U1.1 (C1+)
unnamed: C4.2, U1.4 (C2+)
unnamed: C5.2, U1.6 (V-)
unnamed: LED1.A, R2.2
unnamed: LED2.A, R3.2
unnamed: Q1.1 (C1), Q1.2 (B1), Q1.3 (B2), R4.2
unnamed: J2.2, Q1.6 (E1), Q2.3 (D)
unnamed: Q1.4 (C2), Q2.1 (G), R5.2
unnamed: LED3.A, R6.2
unnamed: LED4.A, R7.2
unnamed: LED5.A, R8.2
R1IN: J1.3, U1.13 (RIN1)
R2IN: JP2.2, U1.8 (RIN2)
RX: LED2.C, SV1.10, U1.12 (ROUT1)
RX_2: LED4.C, SV1.11, U1.9 (ROUT2)
T1OUT: J1.2, U1.14 (DOUT1)
T2OUT: JP2.1, U1.7 (DOUT2)
TX: LED1.C, SV1.8, U1.11 (DIN1)
TX_2: LED3.C, SV1.13, U1.10 (DIN2)

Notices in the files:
parts and their libraries:
SparkFun-Connectors: Licensing: Creative Commons ShareAlike 4.0 International - https://creativecommons.org/licenses/by-sa/4.0
microbuilder: This work is placed in the public domain, and may be freely used for commercial and non-commercial work with the following conditions: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
